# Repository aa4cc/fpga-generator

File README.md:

This readme file is intended as a quick user manual. It does not aim to deliver a full description of the design and inner workings of the generator, as those are provided in a bachelor thesis available from [https://dspace.cvut.cz/handle/10467/92778].

# Generator of phase-shifted square waves

This repository contains a generator of phase-shifted square waves.
The generator is built upon the De0-Nano developement board and implmeneted as a Quartus II. project.

It provides 64 output channels, each with configurable phase shift and duty cycle. The resolution of those parameters is 360 parts per period.
All outputs share a single frequency, which is also reconfigurable on the fly.

Communication to the device is realised via UART.

The design of the device is modular and allows for multiple devices of the same kind to be synchronised together, thus providing more outputs.
When devices are synchronised in this way, they need to be connected via a custom PCB shield designed for this purpose.
Design files for the shield are available in the chaining_shield folder.

For a guide on how to set up the generator, see [Setting up the generator](SETUP.md).

After the generator is set up, see [Communication](COMMUNICATION.md) for details on how to use the generator.

The output pins of the channels of the generator, as well as other pin assignments, are provided in [Mappings](MAPPINGS.md).

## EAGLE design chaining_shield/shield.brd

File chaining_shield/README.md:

View this project on [CADLAB.io](https://cadlab.io/project/2149). 

# fpga_generator_chaining_shield

This is a synchronisation shield for interconnecting up to 4 generators. The coaxial cable connectors labeled M1 to M4 are used as clock outputs in the master device, while the connector labeled S is used as input in both master and slave devices.

When synchronizing multiple (N) devices, all of their boards should be interconnected via a flat cable connecting to the connector labeled SV1. Then, N coaxial cables should be connected to the M connectors of the master device. Connect the other end of each cable to the S input of one of the synchronized devices.

Yes, this includes the master - one of the cables will be connected to an output of the master device and loop back into the input of the master device. This is done to keep the transmission line lengths the same.

The board mates to the bottom (13x2) GPIO header of DE0-Nano. When determining the orientation, make use of the fact that the leftmost pin of the bottom row of header J0 mates to the ground pin of DE0-Nano.

# Notes on populating the board

Not all components shown in the schematic need to be populated. In particular:

* LED1 is optional (it has identical function to LED0 on top of the DE0-Nano kit. If your application lets you easily observe the top of the kit, feel free to skip it, otherwise, it is reccomended).
* Pins J1 and J2 are not used in the design and do not need to be populated.
* Resistor R1 is intended as termination resistor for impedance matching. When the device was tested at 40kHz, it functioned without it, so I left it unpopulated. 
* Coaxial connectors labeled M1 to M4 only need to be populated on the master board. The boards which will be used on slave devices only need their S connector populated. (The master board also needs its S connector populated).

**If you do decide to populate resistor R1**, make sure that you choose a suitably high value!  The pins feeding the clock outputs (labeled M1 to M4) have series 50 ohm resistors enabled in the Quartus project design files. Consult the cyclone IV datasheet to make sure that your chosen value will not decrease the amplitude of the signal below the logic level threshold. (The I/Os operate at 3,3V standard)

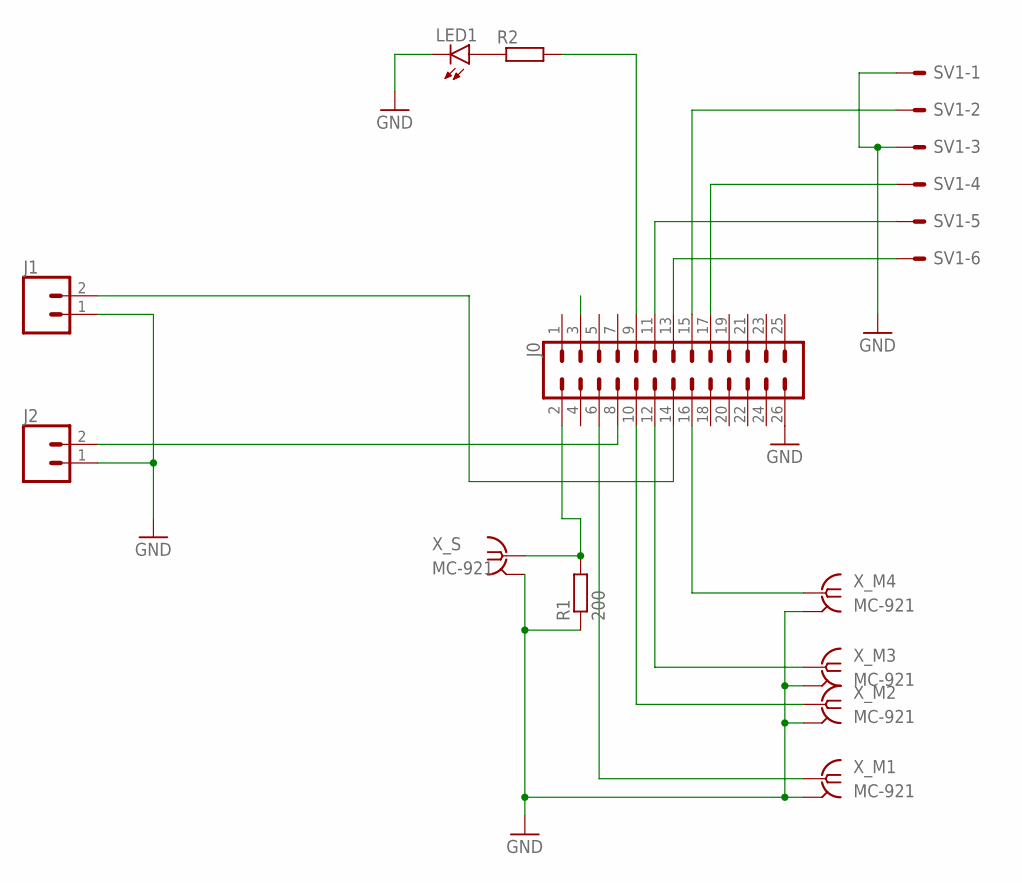
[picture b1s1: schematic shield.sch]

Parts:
J0: CONN_13X22X13; 2X13
J1, J2: CONN_02; 1X02
LED1: LEDCHIPLED_0805; CHIPLED_0805
R1: 200; R0805
R2: R-EU_R0805; R0805
SV1: ML6E; ML6
X_M1, X_M2, X_M3, X_M4: MC-921
X_S: MC-921

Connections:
GND: J0.26, J1.1, J2.1, LED1.C, R1.1, SV1.1, SV1.3, X_M1.2@1 (GND), X_M1.2@2 (GND), X_M2.2@1 (GND), X_M2.2@2 (GND), X_M3.2@1 (GND), X_M3.2@2 (GND), X_M4.2@1 (GND), X_M4.2@2 (GND), X_S.2@1 (GND), X_S.2@2 (GND)
unnamed: J0.2, R1.2, X_S.1
unnamed: J0.6, X_M1.1
unnamed: J0.16, X_M4.1
unnamed: J0.10, X_M2.1
unnamed: J0.12, X_M3.1
unnamed: J0.8, J2.2
unnamed: J0.14, J1.2
unnamed: J0.17, SV1.4
unnamed: J0.15, SV1.2
unnamed: J0.13, SV1.6
unnamed: J0.11, SV1.5
unnamed: LED1.A, R2.1
unnamed: J0.9, R2.2

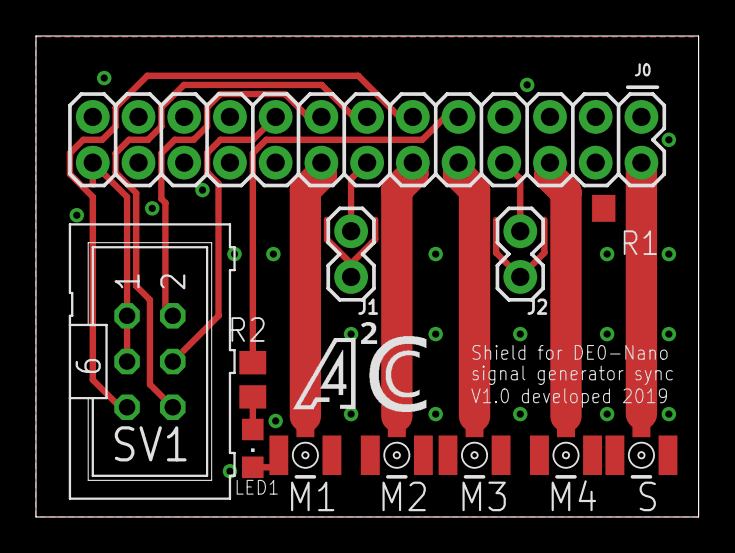
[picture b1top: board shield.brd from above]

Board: 2 copper layers, 36.8 x 26.7 mm, 12 parts (0 on the bottom side), 14 nets.

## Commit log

2019-05-29 FPGA generator for Shield v1.0
2019-05-29 created branch for variable frequency generator
2019-05-30 modified pin assignments to work with Shield v1.1
2019-06-03 Python scripts communicationg with the generator added
2019-06-12 Readme update
    Updated features, description of communication with examples. Added mif file with example for PLL reconfiguration.
    TODO: Output pin mappings
2019-09-09 github fork test
2019-09-10 CLK_freq and CLK_logic outputs for testing basic device sync
2019-09-11 Basic working sync
2019-09-26 WIP on pinout for synchronisation shield V1.0
2019-10-15 wip on pinout for chaining shield
2019-10-17 Ready for use with sync shield
    todo: add possibilty of running as master with no slaves without connecting own clock to itself
2019-10-21 deleted conflicting readme file
2019-10-21 moved Quartus project to subdirectory
2019-10-21 added chaining shield PCB design by Petr Broz
2019-11-07 Moved uart input to pin F16 (uppermost right on chain-shield molex connector)
2019-11-08 Change baud to 115200, added incoming UART signal as output (pin G15)
2019-11-14 WIP on checksum. Addition appears to be working correctly
2019-11-19 Implemented uart checksum
2019-11-26 added checksums to chained generators.
2019-11-29 implement checksums
2019-11-29 Move files misplaced by merge
2019-11-30 Two-way communication wip
    Fully rewritten communication decoder into a more reasonable state-machine.
    implemented CRC-8 on incoming data
    added (for now rudimentary) two way communication (replies to indicate whether CRC was correct or not)
    tested new communication - working (phase shifts not tested, master/slave circuitry bypassed for purposes of test)
2019-12-01 Changes to comm protocol, implement master inquiry
    Implemented a way to ask the device whether it is master or not.
    CRC calc currently broken on this command
    Changes to codes
2019-12-03 Remove parity bit from uart communication
2019-12-03 Implement async resets for channels and counter (prep to move away from having to transmit the 40k CLOCK_FREQ via flat cable)
2019-12-04 fix elusive bug caused by uninitalised signal in uartRec
2019-12-04 Implement new synchronisation via master command
2019-12-05 Fixed bug with incorrect crc calculation of multibyte messages
2019-12-05 Add example of new communication
2019-12-05 Remove oversight left from debugging
2019-12-05 move master setting from jumpers to switch, don't request crc on unknown byte
2019-12-06 Fix issues with UART comms while connected to output shield, change to software-switched master mode
2019-12-06 Add software master control to comms script
2019-12-12 Change pin mappings to shield V1.0
2020-03-01 gitignore binaries
2020-03-01 implement pll reconfiguration
2020-03-02 fix bug in last state of reconfigurator
2020-03-03 implemented pll reconfiguration to V2 comms
2020-03-05 minor schematic tweaks
2020-03-05 add muxes and demuxes for joining chained and unchained versions
2020-03-22 wip on gpio remapping for chained/unchained version switching
2020-04-30 various signal name changes to improve consistency
2020-04-30 fix incorrect generic for clock divider
2020-04-30 remove unused signals from uart
2020-04-30 cut leftover parity logic from uart tx
2020-05-01 bugfix: prevent counter synchronisation from happening if crc not correct
2020-05-01 typo fix
2020-05-22 readme comment
2020-05-22 wip documentation - wip new readme
2020-05-29 create comm. doc file
2020-05-29 typo
2020-11-12 typo fixes and minor improvements to readmes
2021-01-28 add thesis link
2024-06-07 document differences to uart pinout in chained / standalone versions
2024-06-07 remove incorrect pin mapping info

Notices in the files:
parts and their libraries:
SparkFun-Connectors: Licensing: Creative Commons ShareAlike 4.0 International - https://creativecommons.org/licenses/by-sa/4.0
